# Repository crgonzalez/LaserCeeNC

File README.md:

# LaserCeeNC
Team 8 Senior Thesis Project code

Prototype Version 1 - Completed as of 2/10/16

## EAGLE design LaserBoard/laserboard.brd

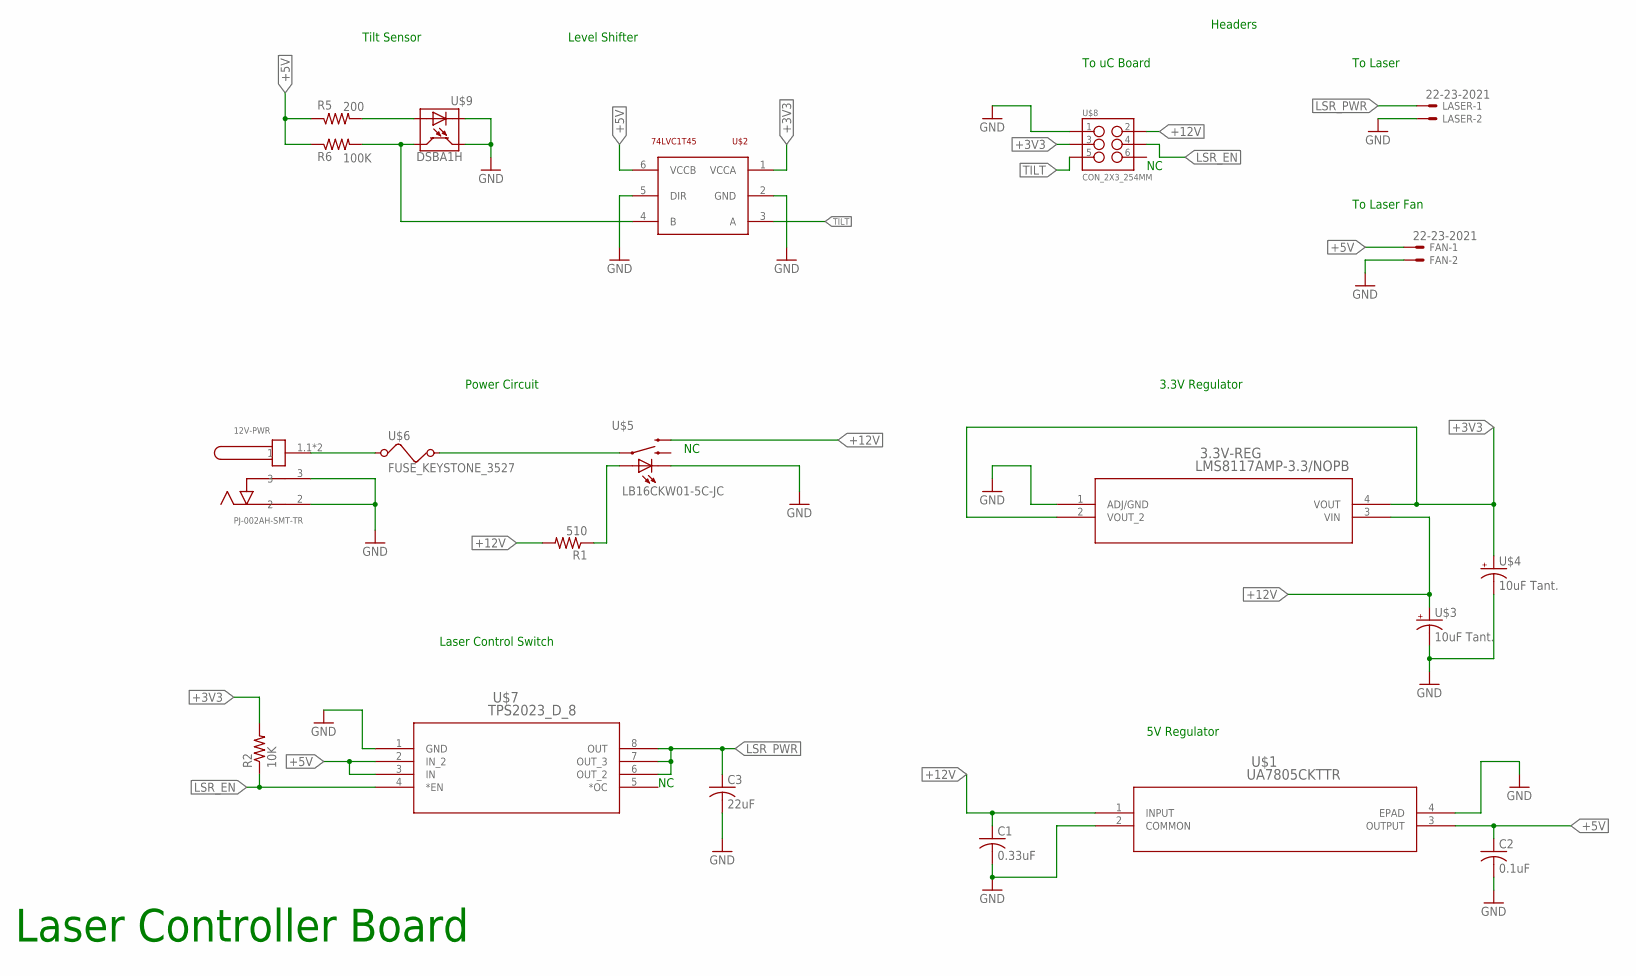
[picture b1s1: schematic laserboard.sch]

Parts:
3.3V-REG: LMS8117AMP-3.3/NOPB; MP04A
12V-PWR: PJ-002AH-SMT-TR; CUI_PJ-002AH-SMT-TR
C1: 0.33uF; C0805
C2: 0.1uF; C0805
C3: 22uF; C0805
FAN: 22-23-2021
LASER: 22-23-2021
R1: 510; R0805
R2: 10K; R0805
R5: 200; R0805
R6: 100K; R0805
U$1: UA7805CKTTR; KTT3_6P22X6P6
U$2: 74LVC1T45; SOT363
U$3, U$4: 10uF Tant.; C0805
U$5: LB16CKW01-5C-JC
U$6: FUSE_KEYSTONE_3527; KEYSTONE3527
U$7: TPS2023_D_8; D8
U$8: CON_2X3_254MM
U$9: DSBA1H

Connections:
+3V3: 3.3V-REG.2 (VOUT_2), 3.3V-REG.4 (VOUT), R2.2, U$2.1 (VCCA), U$4.+, U$8.3
+5V: C2.1, FAN.1, R5.1, R6.1, U$1.3 (OUTPUT), U$2.6 (VCCB), U$7.2 (IN_2), U$7.3 (IN)
+12V: 3.3V-REG.3 (VIN), C1.1, R1.2, U$1.1 (INPUT), U$3.+, U$5.2, U$8.2
GND: 3.3V-REG.1 (ADJ/GND), 12V-PWR.2, 12V-PWR.3, C1.2, C2.2, C3.2, FAN.2, LASER.2, U$1.2 (COMMON), U$1.4 (EPAD), U$2.2 (GND), U$2.5 (DIR), U$3.-, U$4.-, U$5.-, U$7.1 (GND), U$8.1, U$9.-, U$9.E
LSR_EN: R2.1, U$7.4 (*EN), U$8.4
LSR_PWR: C3.1, LASER.1, U$7.6 (OUT_2), U$7.7 (OUT_3), U$7.8 (OUT)
unnamed: R1.1, U$5.+
unnamed: 12V-PWR.1.1 (1), 12V-PWR.1.2 (1), U$6.P$1 (1)
unnamed: U$5.1, U$6.P$2 (2)
unnamed: R6.2, U$2.4 (B), U$9.C
unnamed: R5.2, U$9.+
TILT: U$2.3 (A), U$8.5

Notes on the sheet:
5V Regulator
3.3V Regulator
Power Circuit
Laser Control Switch
Headers
To Laser
To Laser Fan
To uC Board
Tilt Sensor
Level Shifter
Laser Controller Board

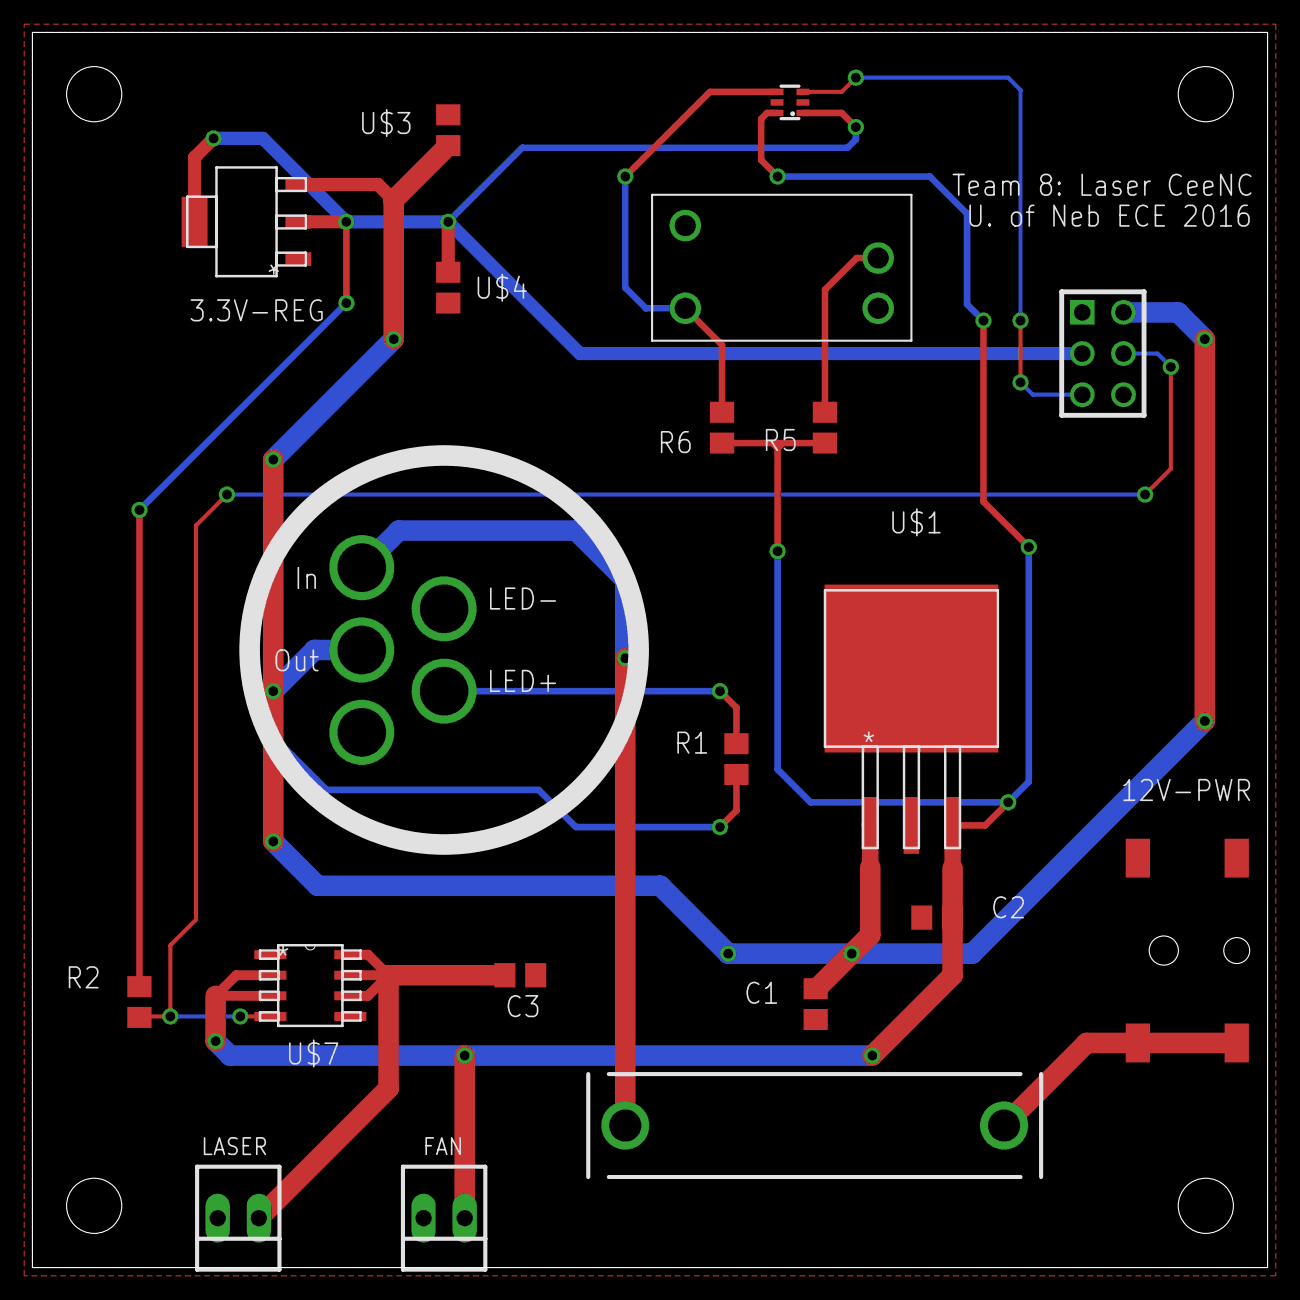
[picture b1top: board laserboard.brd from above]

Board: 2 copper layers, 76.2 x 76.2 mm, 20 parts (0 on the bottom side), 12 nets.

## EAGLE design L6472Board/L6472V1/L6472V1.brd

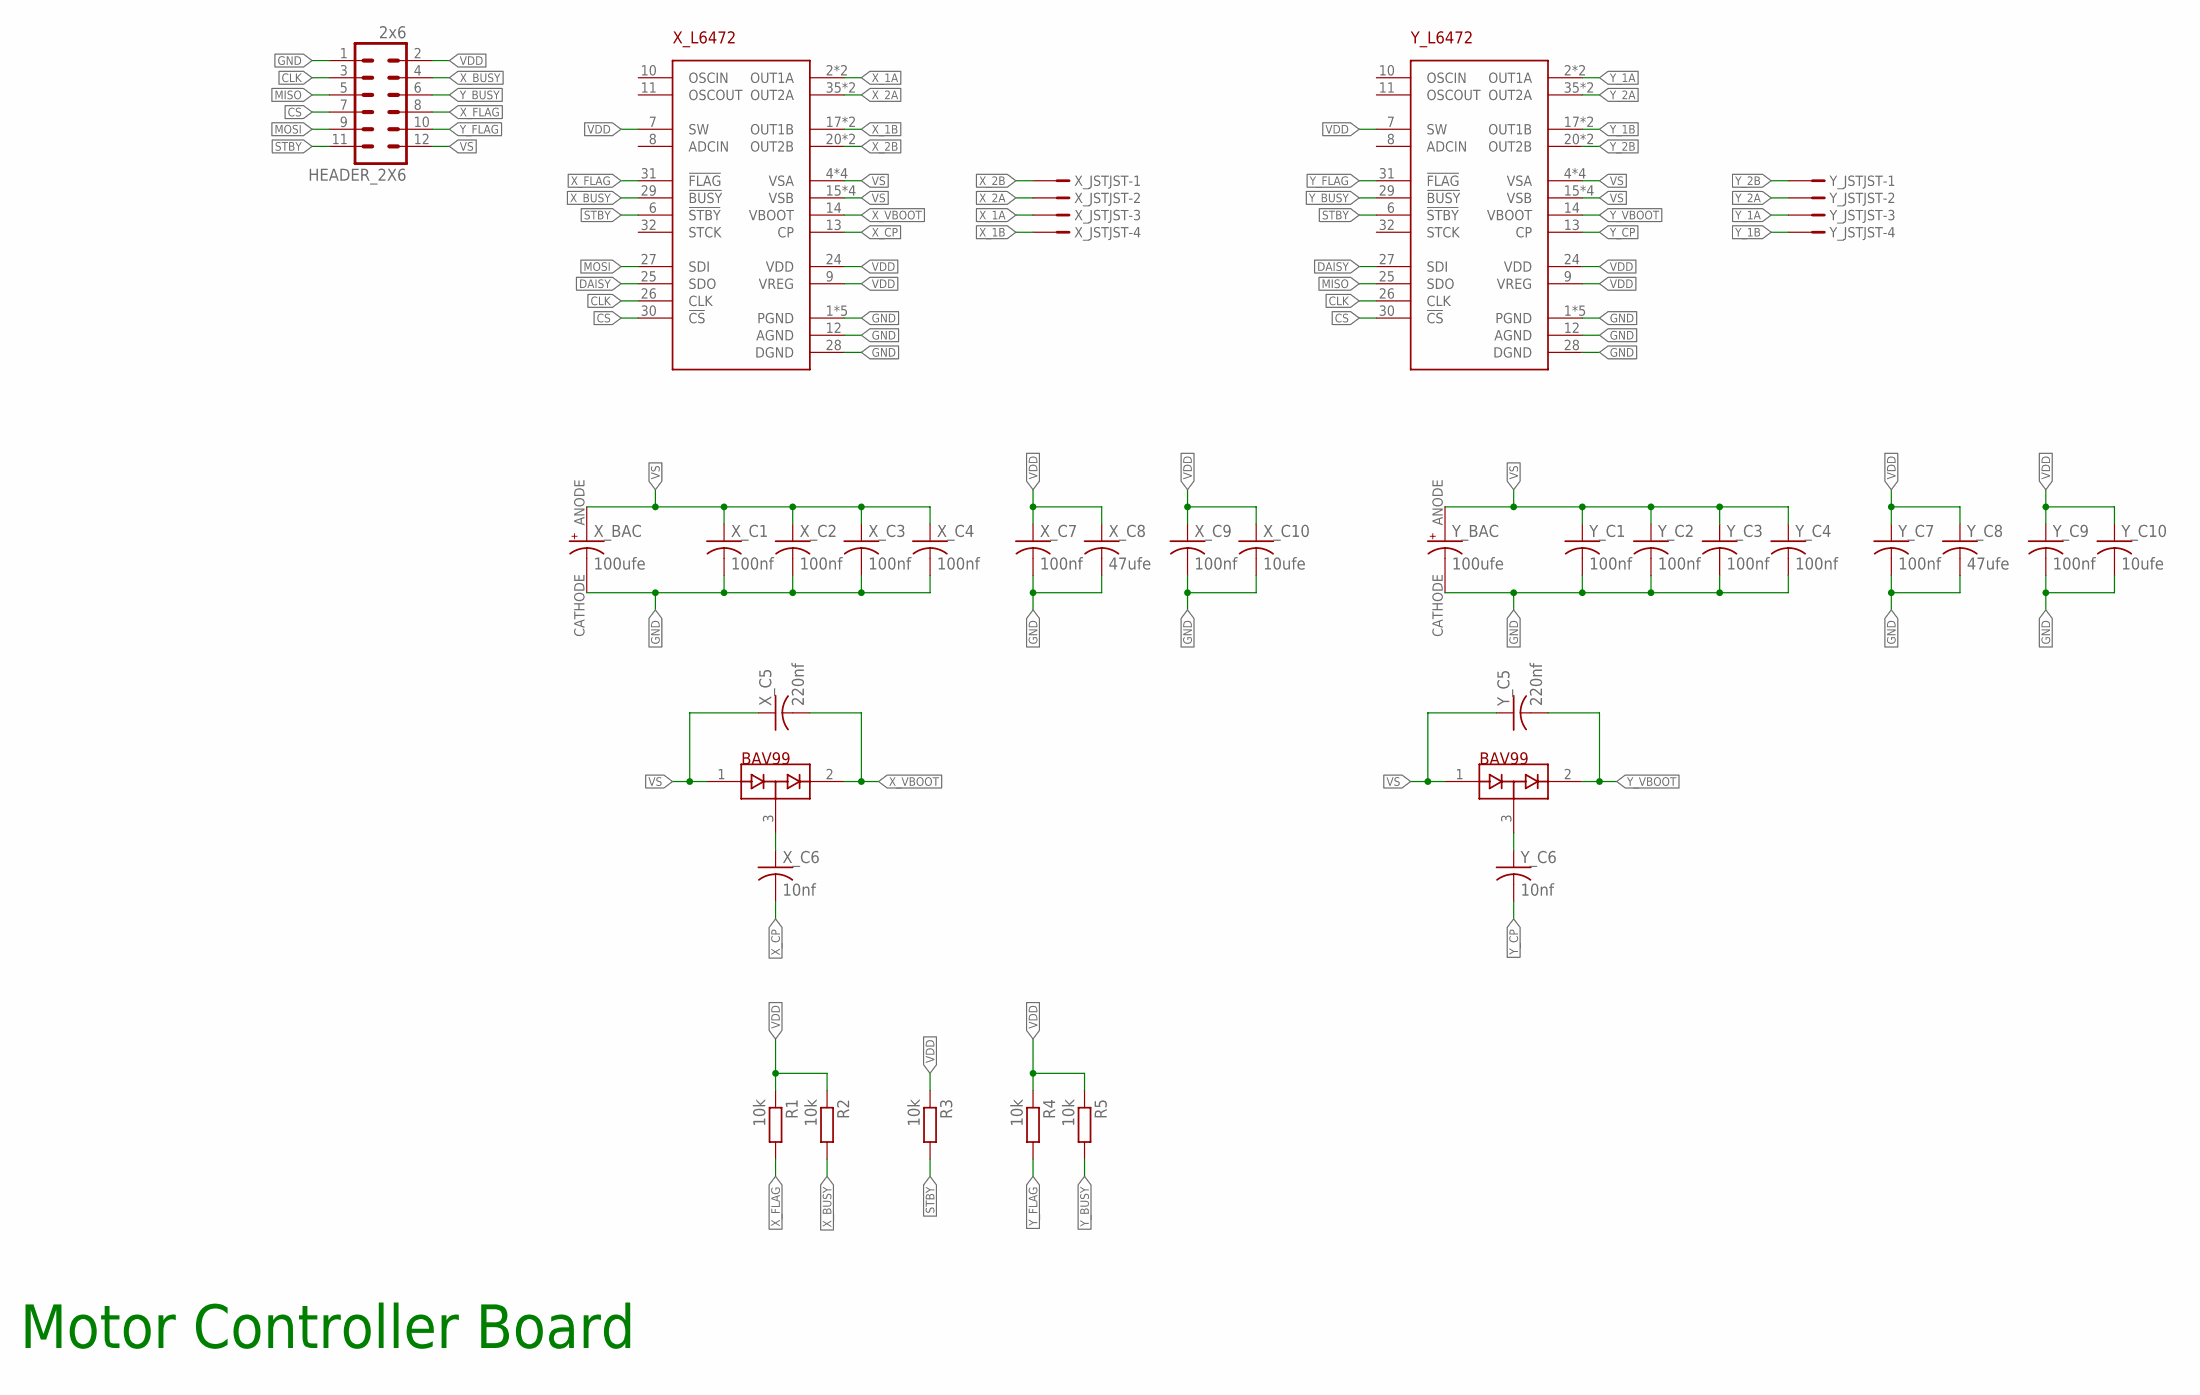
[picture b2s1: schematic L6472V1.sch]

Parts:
HEADER_2X6: 2x6; MA06-2
R1, R2, R3, R4, R5: 10k; M1206
X_BAC: 100ufe; EEE1AA101WR
X_BAV99: BAV99; SOT23_CPL
X_C1, X_C2, X_C3, X_C4, X_C7, X_C9: 100nf; C1206
X_C5: 220nf; C1206
X_C6: 10nf; C1206
X_C8: 47ufe; C1206
X_C10: 10ufe; C1206
X_JST: JST; JST-4
X_L6472: L6472; PSO36
Y_BAC: 100ufe; EEE1AA101WR
Y_BAV99: BAV99; SOT23_CPL
Y_C1, Y_C2, Y_C3, Y_C4, Y_C7, Y_C9: 100nf; C1206
Y_C5: 220nf; C1206
Y_C6: 10nf; C1206
Y_C8: 47ufe; C1206
Y_C10: 10ufe; C1206
Y_JST: JST; JST-4
Y_L6472: L6472; PSO36

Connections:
CLK: HEADER_2X6.3, X_L6472.26 (CLK), Y_L6472.26 (CLK)
CS: HEADER_2X6.7, X_L6472.30 (!CS), Y_L6472.30 (!CS)
DAISY: X_L6472.25 (SDO), Y_L6472.27 (SDI)
GND: HEADER_2X6.1, X_BAC.CATHODE (-), X_C1.2, X_C2.2, X_C3.2, X_C4.2, X_C7.2, X_C8.2, X_C9.2, X_C10.2, X_L6472.1 (PGND), X_L6472.12 (AGND), X_L6472.19 (PGND), X_L6472.28 (DGND), X_L6472.M@1 (PGND), X_L6472.M@2 (PGND), X_L6472.M@3 (PGND), Y_BAC.CATHODE (-), Y_C1.2, Y_C2.2, Y_C3.2, Y_C4.2, Y_C7.2, Y_C8.2, Y_C9.2, Y_C10.2, Y_L6472.1 (PGND), Y_L6472.12 (AGND), Y_L6472.19 (PGND), Y_L6472.28 (DGND), Y_L6472.M@1 (PGND), Y_L6472.M@2 (PGND), Y_L6472.M@3 (PGND)
MISO: HEADER_2X6.5, Y_L6472.25 (SDO)
MOSI: HEADER_2X6.9, X_L6472.27 (SDI)
STBY: HEADER_2X6.11, R3.2, X_L6472.6 (!STBY), Y_L6472.6 (!STBY)
VDD: HEADER_2X6.2, R1.1, R2.1, R3.1, R4.1, R5.1, X_C7.1, X_C8.1, X_C9.1, X_C10.1, X_L6472.7 (SW), X_L6472.9 (VREG), X_L6472.24 (VDD), Y_C7.1, Y_C8.1, Y_C9.1, Y_C10.1, Y_L6472.7 (SW), Y_L6472.9 (VREG), Y_L6472.24 (VDD)
VS: HEADER_2X6.12, X_BAC.ANODE (+), X_BAV99.1 (A1), X_C1.1, X_C2.1, X_C3.1, X_C4.1, X_C5.1, X_L6472.4 (VSA), X_L6472.5 (VSA), X_L6472.15 (VSB), X_L6472.16 (VSB), X_L6472.22 (VSB), X_L6472.23 (VSB), X_L6472.33 (VSA), X_L6472.34 (VSA), Y_BAC.ANODE (+), Y_BAV99.1 (A1), Y_C1.1, Y_C2.1, Y_C3.1, Y_C4.1, Y_C5.1, Y_L6472.4 (VSA), Y_L6472.5 (VSA), Y_L6472.15 (VSB), Y_L6472.16 (VSB), Y_L6472.22 (VSB), Y_L6472.23 (VSB), Y_L6472.33 (VSA), Y_L6472.34 (VSA)
X_1A: X_JST.P2, X_L6472.2 (OUT1A), X_L6472.3 (OUT1A)
X_1B: X_JST.P3, X_L6472.17 (OUT1B), X_L6472.18 (OUT1B)
X_2A: X_JST.P1, X_L6472.35 (OUT2A), X_L6472.36 (OUT2A)
X_2B: X_JST.P0, X_L6472.20 (OUT2B), X_L6472.21 (OUT2B)
X_BUSY: HEADER_2X6.4, R2.2, X_L6472.29 (!BUSY)
X_C1: Y_BAV99.3 (COM), Y_C6.1
X_C6: X_BAV99.3 (COM), X_C6.1
X_CP: X_C6.2, X_L6472.13 (CP)
X_FLAG: HEADER_2X6.8, R1.2, X_L6472.31 (!FLAG)
X_VBOOT: X_BAV99.2 (C2), X_C5.2, X_L6472.14 (VBOOT)
Y_1A: Y_JST.P2, Y_L6472.2 (OUT1A), Y_L6472.3 (OUT1A)
Y_1B: Y_JST.P3, Y_L6472.17 (OUT1B), Y_L6472.18 (OUT1B)
Y_2A: Y_JST.P1, Y_L6472.35 (OUT2A), Y_L6472.36 (OUT2A)
Y_2B: Y_JST.P0, Y_L6472.20 (OUT2B), Y_L6472.21 (OUT2B)
Y_BUSY: HEADER_2X6.6, R5.2, Y_L6472.29 (!BUSY)
Y_CP: Y_C6.2, Y_L6472.13 (CP)
Y_FLAG: HEADER_2X6.10, R4.2, Y_L6472.31 (!FLAG)
Y_VBOOT: Y_BAV99.2 (C2), Y_C5.2, Y_L6472.14 (VBOOT)

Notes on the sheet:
Motor Controller Board

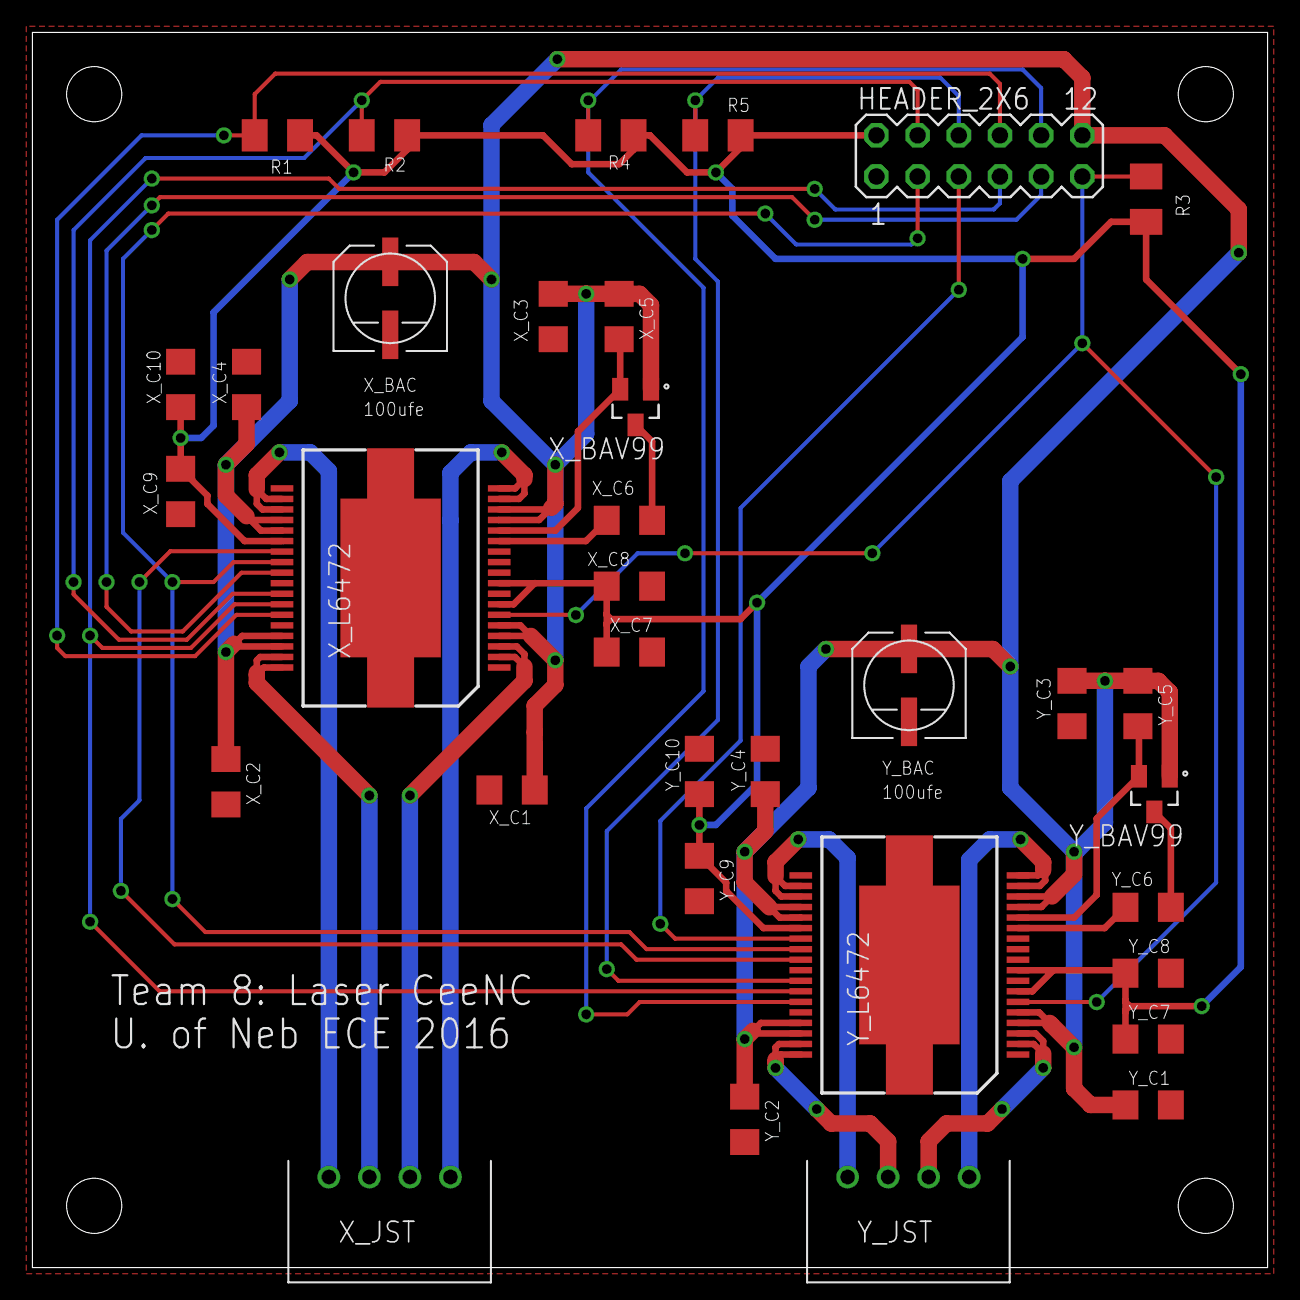
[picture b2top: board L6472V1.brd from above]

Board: 2 copper layers, 76.2 x 76.2 mm, 34 parts (0 on the bottom side), 27 nets.

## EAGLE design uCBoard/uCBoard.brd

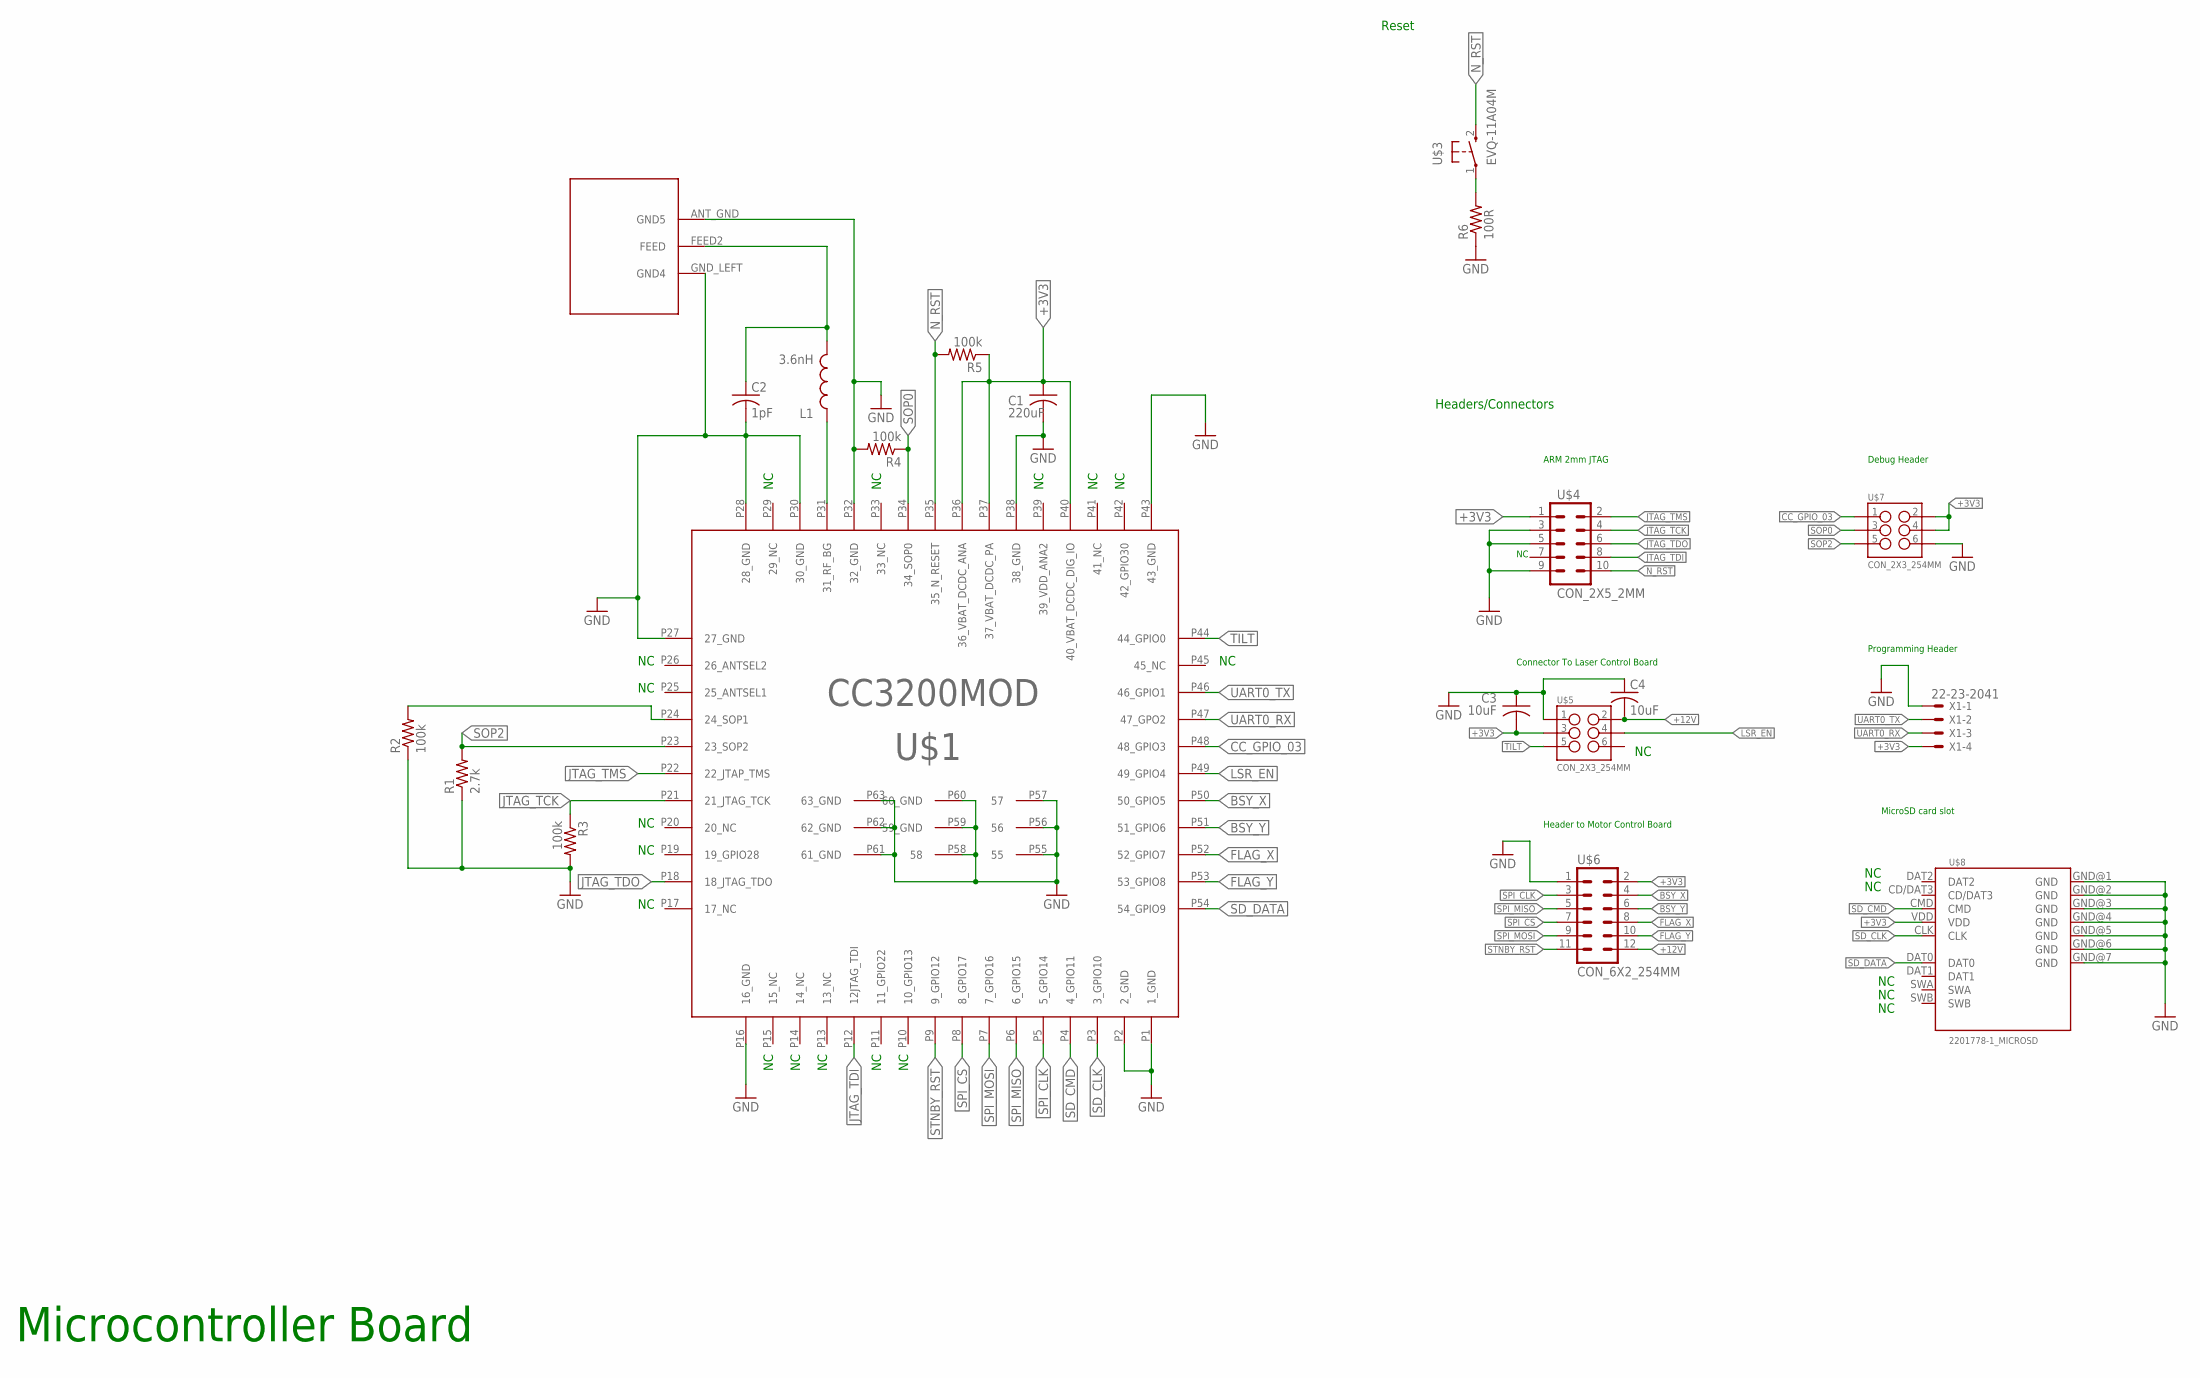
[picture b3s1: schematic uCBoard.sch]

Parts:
C1: 220uF; C1210
C2: 1pF; C0805
C3, C4: 10uF; C0805
L1: 3.6nH; C0402
R1: 2.7k; R0805
R2, R3, R4, R5: 100k; R0805
R6: 100R; R0805
U$1: CC3200; CC3200MOD
U$2: ANT
U$3: EVQ-11A04M; EVQ--11A04M
U$4: CON_2X5_2MM
U$5, U$7: CON_2X3_254MM
U$6: CON_6X2_254MM
U$8: 2201778-1_MICROSD; 2201778-1
X1: 22-23-2041

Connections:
+3V3: C1.1, C3.2, R5.1, U$1.P36 (36_VBAT_DCDC_ANA), U$1.P37 (37_VBAT_DCDC_PA), U$1.P40 (40_VBAT_DCDC_DIG_IO), U$4.1, U$5.3, U$6.2, U$7.2, U$7.4, U$8.VDD, X1.4
+12V: C4.2, U$5.2, U$6.12
BSY_X: U$1.P50 (50_GPIO5), U$6.4
BSY_Y: U$1.P51 (51_GPIO6), U$6.6
CC_GPIO_03: U$1.P48 (48_GPIO3), U$7.1
FLAG_X: U$1.P52 (52_GPIO7), U$6.8
FLAG_Y: U$1.P53 (53_GPIO8), U$6.10
GND: C1.2, C2.2, C3.1, C4.1, R1.1, R2.1, R3.2, R4.2, R6.1, U$1.P1 (1_GND), U$1.P2 (2_GND), U$1.P16 (16_GND), U$1.P27 (27_GND), U$1.P28 (28_GND), U$1.P30 (30_GND), U$1.P32 (32_GND), U$1.P38 (38_GND), U$1.P43 (43_GND), U$1.P55 (55), U$1.P56 (56), U$1.P57 (57), U$1.P58 (58), U$1.P59 (59_GND), U$1.P60 (60_GND), U$1.P61 (61_GND), U$1.P62 (62_GND), U$1.P63 (63_GND), U$2.ANT_GND (GND5), U$2.GND_LEFT (GND4), U$4.3, U$4.5, U$4.9, U$5.1, U$6.1, U$7.6, U$8.GND@1 (GND), U$8.GND@2 (GND), U$8.GND@3 (GND), U$8.GND@4 (GND), U$8.GND@5 (GND), U$8.GND@6 (GND), U$8.GND@7 (GND), X1.1
JTAG_TCK: R3.1, U$1.P21 (21_JTAG_TCK), U$4.4
JTAG_TDI: U$1.P12 (12JTAG_TDI), U$4.8
JTAG_TDO: U$1.P18 (18_JTAG_TDO), U$4.6
JTAG_TMS: U$1.P22 (22_JTAP_TMS), U$4.2
LSR_EN: U$1.P49 (49_GPIO4), U$5.4
unnamed: R6.2, U$3.1
unnamed: L1.1, U$1.P31 (31_RF_BG)
unnamed: R2.2, U$1.P24 (24_SOP1)
unnamed: C2.1, L1.2, U$2.FEED2 (FEED)
N_RST: R5.2, U$1.P35 (35_N_RESET), U$3.2, U$4.10
SD_CLK: U$1.P3 (3_GPIO10), U$8.CLK
SD_CMD: U$1.P4 (4_GPIO11), U$8.CMD
SD_DATA: U$1.P54 (54_GPIO9), U$8.DAT0
SOP0: R4.1, U$1.P34 (34_SOP0), U$7.3
SOP2: R1.2, U$1.P23 (23_SOP2), U$7.5
SPI_CLK: U$1.P5 (5_GPIO14), U$6.3
SPI_CS: U$1.P8 (8_GPIO17), U$6.7
SPI_MISO: U$1.P6 (6_GPIO15), U$6.5
SPI_MOSI: U$1.P7 (7_GPIO16), U$6.9
STNBY_RST: U$1.P9 (9_GPIO12), U$6.11
TILT: U$1.P44 (44_GPIO0), U$5.5
UART0_RX: U$1.P47 (47_GPO2), X1.3
UART0_TX: U$1.P46 (46_GPIO1), X1.2

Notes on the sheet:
Headers/Connectors
Reset
ARM 2mm JTAG
Connector To Laser Control Board
Header to Motor Control Board
Debug Header
Programming Header
MicroSD card slot
Microcontroller Board

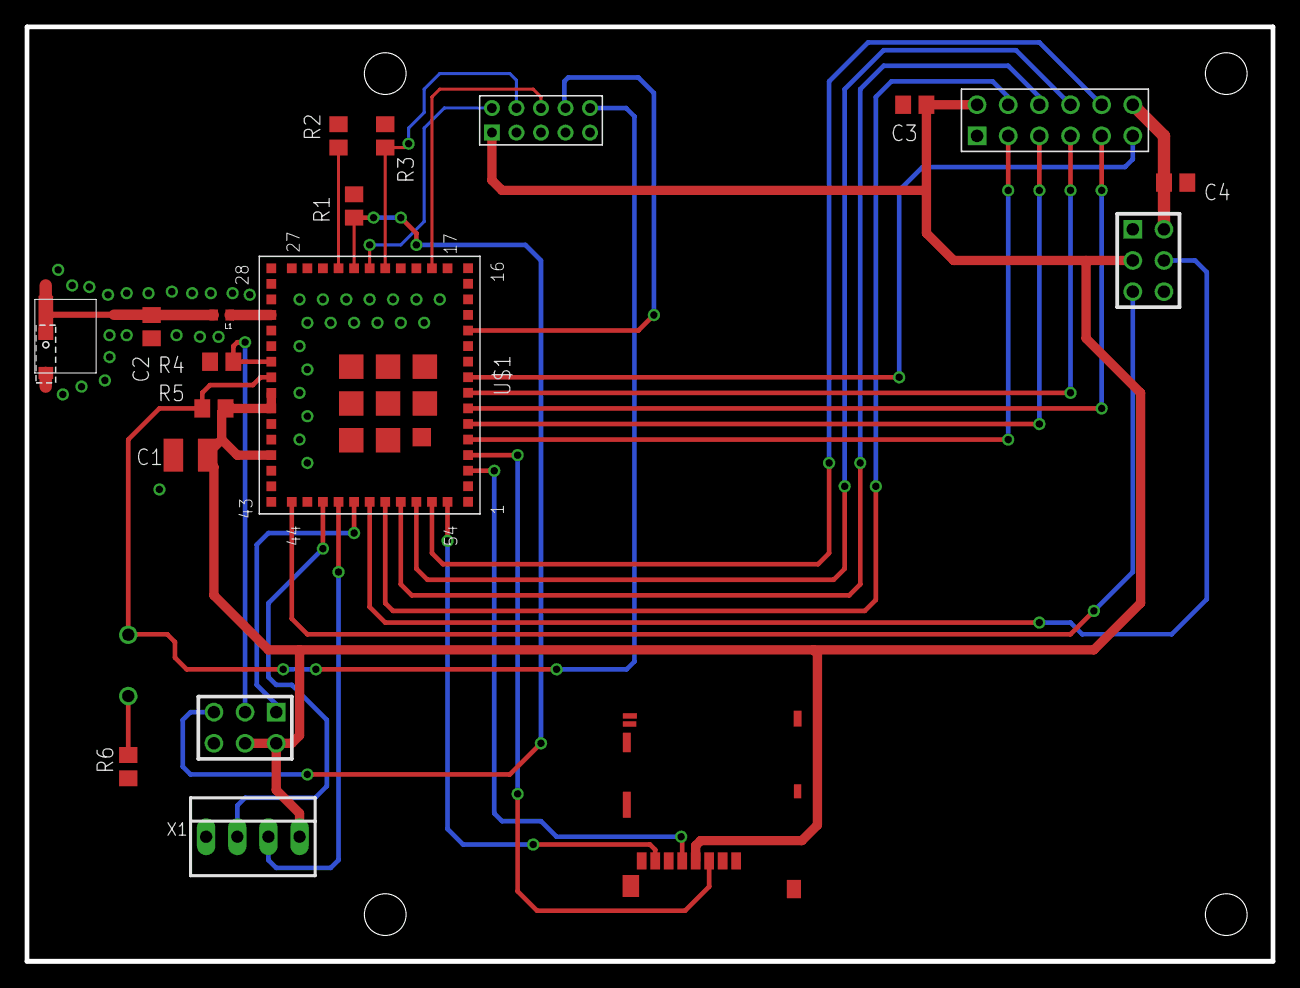
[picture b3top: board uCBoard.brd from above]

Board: 2 copper layers, 101.6 x 76.2 mm, 20 parts (0 on the bottom side), 31 nets.

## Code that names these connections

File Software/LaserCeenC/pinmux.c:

//*****************************************************************************
// pinmux.c 
// 
// Configure the device pins for different peripheral signals
// 
// Copyright (C) 2014 Texas Instruments Incorporated - http://www.ti.com/ 
// 
// 
//  Redistribution and use in source and binary forms, with or without 
//  are met:
//
//    Redistributions of source code must retain the above copyright 
//    notice, this list of conditions and the following disclaimer.
//
//    Redistributions in binary form must reproduce the above copyright
//    notice, this list of conditions and the following disclaimer in the 
//    documentation and/or other materials provided with the   
//    distribution.
//
//    Neither the name of Texas Instruments Incorporated nor the names of
//    its contributors may be used to endorse or promote products derived
//    from this software without specific prior written permission.
//
//  THIS SOFTWARE IS PROVIDED BY THE COPYRIGHT HOLDERS AND CONTRIBUTORS 
//  "AS IS" AND ANY EXPRESS OR IMPLIED WARRANTIES, INCLUDING, BUT NOT 
//  LIMITED TO, THE IMPLIED WARRANTIES OF MERCHANTABILITY AND FITNESS FOR
//  A PARTICULAR PURPOSE ARE DISCLAIMED. IN NO EVENT SHALL THE COPYRIGHT 
//  OWNER OR CONTRIBUTORS BE LIABLE FOR ANY DIRECT, INDIRECT, INCIDENTAL, 
//  SPECIAL, EXEMPLARY, OR CONSEQUENTIAL DAMAGES (INCLUDING, BUT NOT 
//  LIMITED TO, PROCUREMENT OF SUBSTITUTE GOODS OR SERVICES; LOSS OF USE,
//  DATA, OR PROFITS; OR BUSINESS INTERRUPTION) HOWEVER CAUSED AND ON ANY
//  THEORY OF LIABILITY, WHETHER IN CONTRACT, STRICT LIABILITY, OR TORT 
//  (INCLUDING NEGLIGENCE OR OTHERWISE) ARISING IN ANY WAY OUT OF THE USE 
//  OF THIS SOFTWARE, EVEN IF ADVISED OF THE POSSIBILITY OF SUCH DAMAGE.
//
//*****************************************************************************

//*****************************************************************************
// This file was automatically generated on 7/21/2014 at 3:06:20 PM
// by TI PinMux version 3.0.334
//
//*****************************************************************************

#include "pinmux.h"
#include "hw_types.h"
#include "hw_memmap.h"
#include "hw_gpio.h"
#include "pin.h"
#include "rom.h"
#include "rom_map.h"
#include "gpio.h"
#include "prcm.h"

//*****************************************************************************
void
PinMuxConfig(void)
{
    //
    // Enable Peripheral Clocks
    //
    MAP_PRCMPeripheralClkEnable(PRCM_UARTA0, PRCM_RUN_MODE_CLK);
    MAP_PRCMPeripheralClkEnable(PRCM_GPIOA0, PRCM_RUN_MODE_CLK);
    MAP_PRCMPeripheralClkEnable(PRCM_GPIOA1, PRCM_RUN_MODE_CLK);
    MAP_PRCMPeripheralClkEnable(PRCM_SDHOST, PRCM_RUN_MODE_CLK);

    //
    // Configure PIN_55 for UART0 UART0_TX
    //
    MAP_PinTypeUART(PIN_55, PIN_MODE_3);

    //
    // Configure PIN_57 for UART0 UART0_RX
    //
    MAP_PinTypeUART(PIN_57, PIN_MODE_3);

    //
    // Configure PIN_58 for GPIOInput
    //
    MAP_PinTypeGPIO(PIN_58, PIN_MODE_0, false);
    MAP_GPIODirModeSet(GPIOA0_BASE, 0x8, GPIO_DIR_MODE_IN);

    //
    // Configure PIN_64 for GPIOOutput
    //
    MAP_PinTypeGPIO(PIN_64, PIN_MODE_0, false);
    MAP_GPIODirModeSet(GPIOA1_BASE, 0x2, GPIO_DIR_MODE_OUT);

    //
    // Configure PIN_01 for GPIOOutput
    //
    MAP_PinTypeGPIO(PIN_01, PIN_MODE_0, false);
    MAP_GPIODirModeSet(GPIOA1_BASE, 0x4, GPIO_DIR_MODE_OUT);

    //
    // Configure PIN_02 for GPIOOutput
    //
    MAP_PinTypeGPIO(PIN_02, PIN_MODE_0, false);
    MAP_GPIODirModeSet(GPIOA1_BASE, 0x8, GPIO_DIR_MODE_OUT);

    //
	// Configure PIN_50 for GPIO Input (TILT)
	//
	MAP_PinTypeGPIO(PIN_50, PIN_MODE_0, false);
	MAP_GPIODirModeSet(GPIOA0_BASE, 0x1, GPIO_DIR_MODE_IN);


    //
    // Configure PIN_64 for SDHOST0 SDHost_D0
    //
    //MAP_PinTypeSDHost(PIN_64, PIN_MODE_6);

    //
    // Configure PIN_01 for SDHOST0 SDHost_CLK
    //
    //MAP_PinTypeSDHost(PIN_01, PIN_MODE_6);

    //
    // Configure PIN_02 for SDHOST0 SDHost_CMD
    //
    //MAP_PinTypeSDHost(PIN_02, PIN_MODE_6);
}

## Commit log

2016-01-17 Isaac's Test Commit
    This is a test of the emergency test commit network.
2016-01-17 Group Test Commit
    Test Commit
2016-01-23 Adding Motor Controller Board Eagle Project
    This adds the Eagle files for the Motor Controller Board.
    L6742LIB.lbr holds several footprints and custom components needed by
    the project.
    L6472V1.brd is the board file for laying out the PCB.
    L6472V1.sch is the schematic file for the board.
    eagle.epf is a file created by Eagle. Not sure what it does but it seems
2016-01-23 Completed Routing of PCB
    The layout of the L6472 PCB was completed.
2016-01-25 Initial Schematic Commit
2016-01-30 Fixing custom lib silkscreens
2016-01-31 Layed out uC Board, not yet routed
2016-01-31 Routed majority of uC Board
2016-02-01 Added GND plane and fixed the SD card footprint
2016-02-02 Preliminary Component Placement
    All of the components have been placed onto the 3x3 outline in their
    general location.
2016-02-02 Utilized Christian's Updated Library
    Reloaded ChristiansCustom library to make use of the updated components
    submitted by Christian.
2016-02-03 Completed Layout of the Laser PCB
    This is the completed layout of the Laser PCB. All components and traces
    have been laid. The final DRC before manufacturing has not been
    performed.
2016-02-03 Finished the uCBoard, added custom CAM processor, and created Gerber files
2016-02-07 Final Laser Board Revision
    This commit includes the final revisions Isaac will make on the Laser
    Board. Christian will be consulted before the board is manufactured.
2016-02-07 Final motor controller
    This is the final layout of the motor controller board before
    manufacturing.
2016-02-09 Committing gerber files
2016-02-11 Fixing schematics for design review, adding block diagram, upgrading version to prototype version 2
2016-02-14 TI-RTOS Plugin
2016-02-14 ServicePack Files
2016-02-19 User to CC3200 Communication through Webpage
2016-02-28 Fixing labeling on the uC board so that SPI is correct
2016-02-28 Adding software folder for group collaboration on CCS projects
2016-02-28 Created New Footprints
    Footprints:
    JST
    BAC
2016-02-29 More
2016-02-29 Software v1.0
    User to CC3200 Communication through Webpage
2016-02-29 v1.0.1
2016-02-29 Fixing airwire on uCboard debug header
2016-03-01 v1.0
2016-03-01 Software v1.0
    CC3200 has server capabilities and a single computer can connect to it
    load up the webpage and send a small file through to the processor.
2016-03-01 Revision of Motorcontroller Board
    Footprints for the stepper motor connectors and BACs were replaced.
2016-03-01 Updates to Laser and Power Board
    Updated emergency shutoff button footprint, led button voltage changed
    to 5v, and switched level shifter to 74LVC1T45.
2016-03-10 Final Revisions to PCBs and Schematics
    Final revisions made to the PCBs and schematics. This is the version
    which will be sent out to the board house for round two.
2016-03-12 Basic SPI Setup
    This is the first working spi setup. You can basically hardcode bytes to
    send over spi. More to come soon
2016-03-13 End of the night push
    This code adds some functionality to the L6472 library including reading
    and writing to the x and y devices. There is a bug when reading where
    bits are being doubled. Very stupid. I'm giving up for the night.
2016-03-13 Fixed Bit Doubling Bug
    Fixed a bug with the incoming spi where bits were being counted double.
    Not entirely sure what fixed the issue but it is gone now so whatevs.
2016-03-13 Added a few y axis functions
    Added functions for setting a few y axis parameters as well as run and
    move commands.
2016-03-16 Basic Y Busy Signal GPIO Setup
    The basic structure for reading the Y Busy signal has been setup. There
    is an issue with the GPIO pin pulling the Busy signal from the L6472
    low. Committing before I try changing to a different GPIO pin.
2016-03-16 y_move() and y_wait are working!
2016-03-16 Messed around with motorcontroller and frame
2016-03-17 Stash Changes
2016-03-18 Laser Functions Work
    Functions for configuring and toggling a pin for control of the laser.
2016-03-18 Refactored all initialization into init functions
    Moved all of the initialization code from the example program into the init functions.
2016-03-18 Added y axis mm move function
    Added y_move_mm() which uses a float value of millimeters to define the stepper movements.
    For this to work, the spi_demo project floating point setting must be changed to "vfplib".
2016-03-19 Laser and Motor Libraries Pretty Much Done
    This includes most of the useful laser and motor control functions.
    L6472.h and LaserBoard.h should be added to your project along with
    their equivalent .c files. The y functions have been tested but the x
    have not.
2016-03-26 Added SD Card functions
2016-03-27 X and Y motor controllers working
    Basic x and y control established
2016-03-27 Full File Transfer to CC3200
    Code is capable of taking full text file and transferring it to the
    CC3200
2016-03-27 Register Access Functions
    Added functions for reading register values.
2016-03-27 Laser and Motorcontrol GPIOs Configured
    The laser and motorcontrol gpios are configured and work correctly.
2016-03-27 PSSC G-Code File
    Will test Circle Diamond Square design on CNC machine for accuracy
    verification
2016-03-29 Adding Final BOMS
2016-03-30 Updating Pinmux to include all pin configurations in use
2016-03-30 Adding code for tilt interrupt
2016-04-01 Move to Coordinate Added
    Added move_coord() which allows the motors to move to a specific
    coordinate in a straight line.
2016-04-02 File Operations
    Can save file from website and reopen it and is currently set to just
    print the lines back out on the screen
2016-04-02 G Code Functions
    Merging this functions for zach to use
2016-04-02 Includes spi_demo files
2016-04-02 Diamond Square Hardcode
    Hardcoded dimond square test
2016-04-02 Fixed xy_move_mm() bug
    xy_move_mm() was not executing moves when the x or y movement was zero.
    This was fixed by updating the control structure inside the function to
    include these cases.
2016-04-02 Fixed move_coord() bug
    Fixed issue with diagonal moves with a side less than 0.1 mm. This is a
    crappy fix that ignores moves less than 0.1mm. This needs to be revised
    to prevent the accumulation of errors.
2016-04-02 Updated move_coord() function
    Simplified the operation of the move_coord() function
2016-04-03 Arc functions almost work
    See title
2016-04-03 Edited arc functions
    Starting to include code to prevent skipping a full circle.
2016-04-03 Gcode functions work
    Gcode functions work and are ready to integrated with the parser
2016-04-03 Updated webpage to processing code
2016-04-03 Fully operational now
    Code goes through the entirety of the flow needed to draw a design just
    need to correct how it divides the file for reading and also a way for
    it to go back to HttpServerTask
2016-04-03 Web to processing code
    Edit to adjust division of file, it still needs a little more work but
    is ready for testing
2016-04-03 Full project code
    Works for the most part, issue with circle etch
2016-04-04 Additional code added for G3 instruction
2016-04-04 Fixed Offset Issue in Arc Functions
    Amended the arc functions to properly use the I and J values as offsets
    from the starting point to find the center.
2016-04-05 Trying new target config file
2016-04-05 Tilt Sensor
    Added tilt sensor code to the project.
2016-04-07 I don't know what this change is
2016-04-24 Updating BOM to reflect new regulator

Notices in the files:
parts and their libraries:
COPYRIGHT: Copyright (C) 2015 Accelerated Designs. All rights reserved
SparkFun-Passives: Licensing: Creative Commons ShareAlike 4.0 International - https://creativecommons.org/licenses/by-sa/4.0
